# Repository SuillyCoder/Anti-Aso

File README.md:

<h2>Anti-Aso</h2>
<h4>An Arduino-Powered Ultrasonic Dog-Deterrent made Fit for Household Use</h4>

<p>Okay so, long story short, mama wanted a way to ward off dogs with ultrasonic sound to reduce manual intervention for dog warding. Right now, I just made simulations. Pretty soon, I'll make it into actuality when I get the components and get to test it out in real life. For now, take these photos:</p>
<br>

<h2> Tinkercad Simulation </h2>

<h2> KiCad Schematic </h2>

<h2> Proteus Firmware Project </h2>

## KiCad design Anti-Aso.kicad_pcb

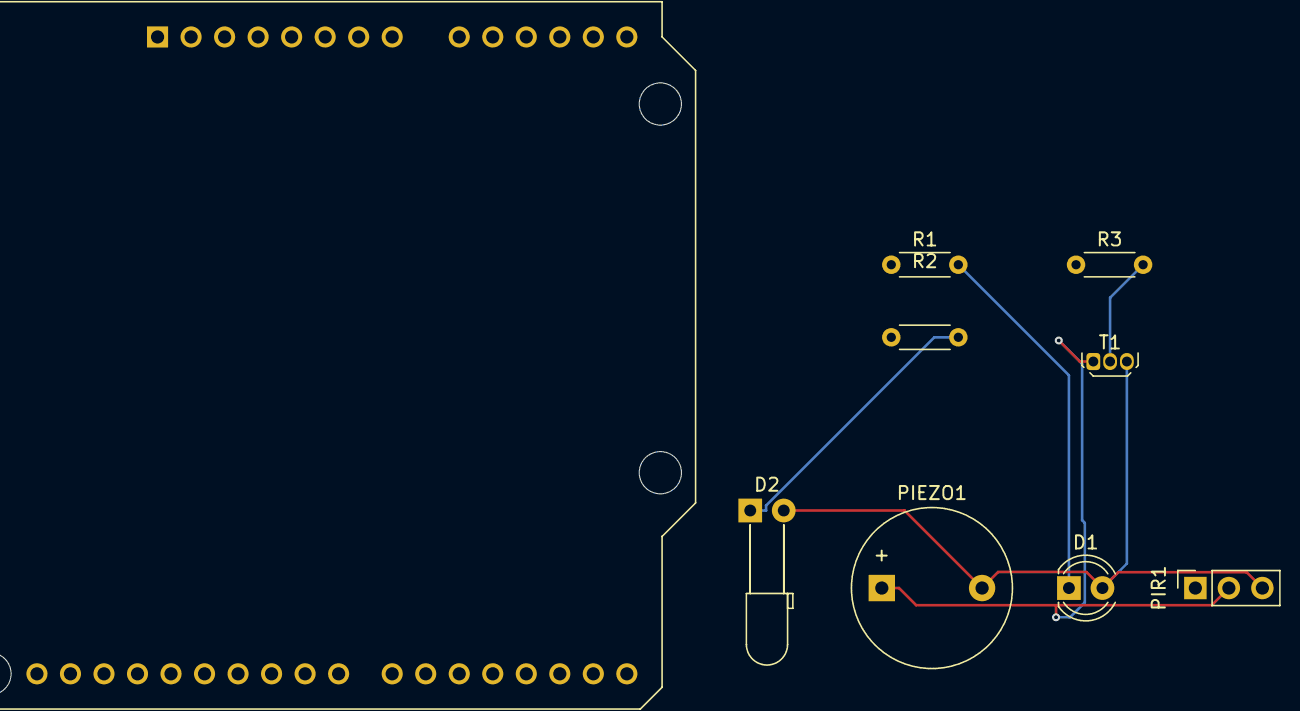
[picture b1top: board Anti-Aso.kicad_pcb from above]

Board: 2 copper layers, 9 parts (0 on the bottom side), 5 nets.

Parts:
D1: RED; LED_D4.0mm
D2: BLUE; LED_D3.0mm_Horizontal_O6.35mm_Z10.0mm
PIEZO1: PIEZO; Buzzer_12x9.5RM7.6
PIR1: PIR-SENSOR_28027; PinSocket_1x03_P2.54mm_Vertical
R1, R2: 100; R_Axial_DIN0204_L3.6mm_D1.6mm_P5.08mm_Horizontal
R3: 1k; R_Axial_DIN0204_L3.6mm_D1.6mm_P5.08mm_Horizontal
T1: NPN; TO-92Flat
U1: ARDUINO-UNO-R3-SHIELD; Arduino_UNO_R3_WithMountingHoles

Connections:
unnamed: D1.1 (A), R1.2
unnamed: D2.1 (A), R2.2
unnamed: R3.2, T1.2 (B)
U1_5V: PIEZO1.1, PIR1.2 (VCC), T1.1 (C)
U1_GND: D1.2 (C), D2.2 (C), PIEZO1.2, PIR1.3 (GND), T1.3 (E)

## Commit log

2026-01-15 Added proteus file, kicad schematic, pcb, arduino sketch, and tinkercad image to initial folder
    Added proteus file, kicad schematic, pcb, arduino sketch, and tinkercad image to initial folder
2026-01-15 I just realizd the PCB File was kind of unneccesary, lmao
    I just realizd the PCB File was kind of unneccesary, lmao
